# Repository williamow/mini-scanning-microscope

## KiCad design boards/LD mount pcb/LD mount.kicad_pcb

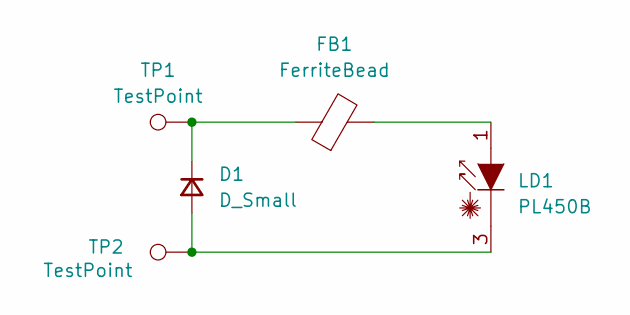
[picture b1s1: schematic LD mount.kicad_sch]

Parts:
D1: D_Small; D_SOD-123F
FB1: FerriteBead; L_0603_1608Metric_Pad1.05x0.95mm_HandSolder
LD1: PL450B; LaserDiode_TO38ICut-3
TP1, TP2: TestPoint; TestPoint_Pad_D2.0mm

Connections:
unnamed: D1.2 (A), LD1.3 (C), TP2.1
unnamed: D1.1 (K), FB1.1, TP1.1
unnamed: FB1.2, LD1.1 (A)

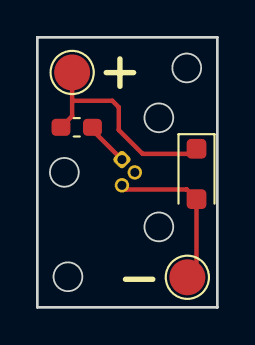
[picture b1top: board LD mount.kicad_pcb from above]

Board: 2 copper layers, 10.0 x 15.0 mm, 5 parts (1 on the bottom side), 3 nets.

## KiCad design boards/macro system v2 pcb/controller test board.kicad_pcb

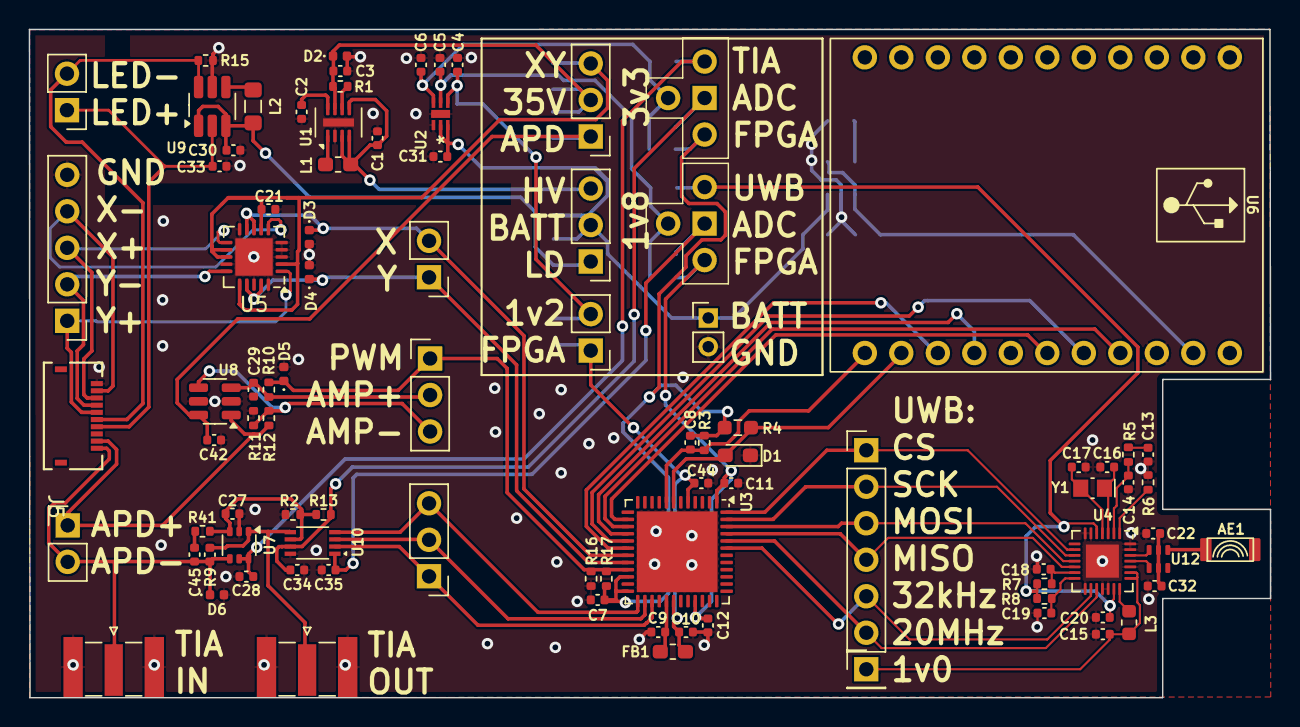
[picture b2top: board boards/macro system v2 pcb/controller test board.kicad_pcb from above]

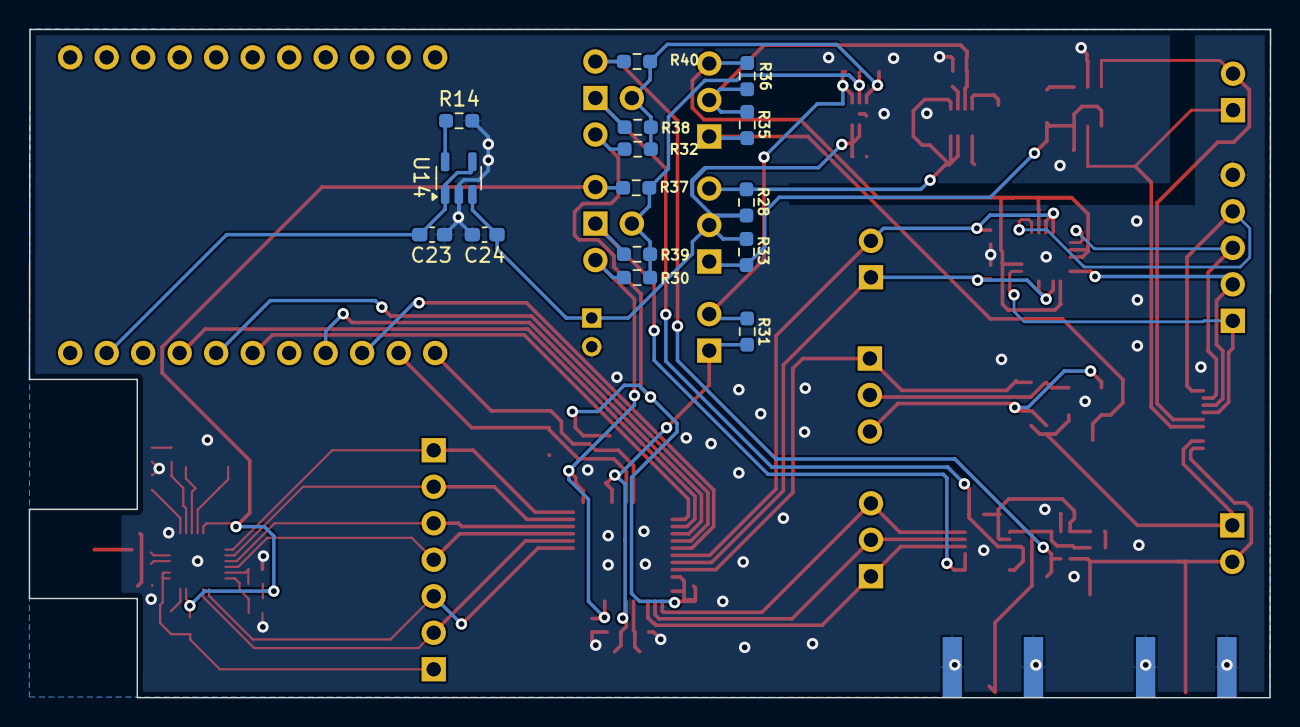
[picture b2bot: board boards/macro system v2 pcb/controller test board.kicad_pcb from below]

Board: 2 copper layers, 86.4 x 46.5 mm, 106 parts (15 on the bottom side), 69 nets.

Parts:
AE1: Antenna; antenna_footprint
C1, C3, C4, C5, C6, C15, C30, C31, C33: 1u; C_0402_1005Metric
C2: 0.22u; C_0402_1005Metric
C7, C9, C10, C11, C12, C18, C19, C20, C21, C22, C27, C28, C29, C32, C34, C35, C42, C44: 100n; C_0402_1005Metric
C8: 12p; C_0402_1005Metric
C13: 680p; C_0402_1005Metric
C14: 68p; C_0402_1005Metric
C16, C17: 3.9p; C_0402_1005Metric
C23, C24: 1u; C_0603_1608Metric_Pad1.08x0.95mm_HandSolder
C45: 50p; C_0402_1005Metric
D1: LED; LED_0603_1608Metric_Pad1.05x0.95mm_HandSolder
D2, D3, D4, D5, D6: D; D_0402_1005Metric
FB1: FerriteBead_Small; L_0603_1608Metric_Pad1.05x0.95mm_HandSolder
J1: Conn_01x02; PinHeader_1x02_P2.00mm_Vertical
J2, J6, J10, J11: Conn_01x03; PinHeader_1x03_P2.54mm_Vertical
J3, J14: Conn_Coaxial; SMA_Samtec_SMA-J-P-X-ST-EM1_EdgeMount
J4: Conn_01x06; PinHeader_1x06_P2.54mm_Vertical
J5: FH19C-10S-0.5SH10; CONN_FH19C-10S-0.5SH10_HIR
J7: Mirror drive; PinHeader_1x05_P2.54mm_Vertical
J8: mdrive; PinHeader_1x02_P2.54mm_Vertical
J9: APD_conn; PinHeader_1x02_P2.54mm_Vertical
J12: Conn_01x02; PinHeader_1x02_P2.54mm_Vertical
J15: LED conn; PinHeader_1x02_P2.54mm_Vertical
J16: Conn_01x01; PinHeader_1x01_P2.54mm_Vertical
L1: 15u; L_0603_1608Metric_Pad1.05x0.95mm_HandSolder
L2: 4.7u; L_0805_2012Metric_Pad1.05x1.20mm_HandSolder
L3: 180n; L_0603_1608Metric
R1: 5M; R_0402_1005Metric
R2, R10, R11, R13: 100k; R_0402_1005Metric
R3, R16, R17: 10k; R_0402_1005Metric
R4: 1k; R_0603_1608Metric_Pad0.98x0.95mm_HandSolder
R5: 390k; R_0402_1005Metric
R6: 2.2M; R_0402_1005Metric
R7: 380k; R_0402_1005Metric
R8: 0; R_0402_1005Metric
R9: TIA_FB; C_0402_1005Metric
R12: 1.2M; R_0402_1005Metric
R14: 10k; R_0603_1608Metric_Pad0.98x0.95mm_HandSolder
R15: 4.7; R_0402_1005Metric
R28, R30, R31, R32, R33, R35, R36, R37, R38, R39, R40: 1; R_0603_1608Metric_Pad0.98x0.95mm_HandSolder
R41: 50; R_0402_1005Metric
U1: LT3494; DFN-8-1EP_2x3mm_P0.5mm_EP0.56x2.15mm
U2: MIC5387-SG4YMT-TR; MLF-6_MT_MCH
U3: ICE40UP5K-SG48ITR; QFN-48-1EP_7x7mm_P0.5mm_EP5.6x5.6mm
U4: SR10x0; QFN-28-1EP_4x4mm_P0.4mm_EP2.3x2.3mm
U5: ADG5234_QFN; QFN-20-1EP_4x4mm_P0.5mm_EP2.6x2.6mm
U6: adafruit_FT232H
U7: OPA838SIDCKT; SOT-363_SC-70-6
U8: ADA4097; TSOT-23-6
U9: AP3036B; SOT-23-6_Handsoldering
U10: ADS7040xDCU; VSSOP-8_2.3x2mm_P0.5mm
U11, U13: Pin-T
U12: CSP_BALUN
U14: MCP73812T-420I-OT; SOT-23-5
Y1: 32.768kHz; Crystal_SMD_MicroCrystal_CM9V-T1A-2Pin_1.6x1.0mm_HandSolder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

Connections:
/1v2: C4.1, J12.2, R31.1, U2.4 (OUT3)
/1v8: C5.1, R30.1, R37.1, R39.2, U2.5 (OUT2), U13.3
/3v3: C6.1, R32.2, R38.2, R40.1, U2.6 (OUT1), U11.3
/35v: C3.1, D2.1 (K), J10.2, R1.2, R35.1, R36.1, U1.7 (VOUT)
/ADC/CS: J6.3, U3.25 (IOT_36b), U10.4 (~CS)
/ADC/SCLK: J6.1, U3.27 (IOT_38b), U10.2 (SCLK)
/ADC/SDO: J6.2, U3.26 (IOT_39a), U10.3 (SDO)
/ADC/ref: C27.1, R2.1, R13.1, R41.2, U7.3 (+), U10.6 (AINP)
/ADC/vin: J3.1 (In), R9.2, U7.1, U10.5 (AINM)
/ADG5234/INX: D3.1 (K), J8.2, U3.19 (IOB_29b), U5.8 (IN2), U5.9 (IN3)
/ADG5234/INY: D4.1 (K), J8.1, U3.20 (IOB_25b_G3), U5.17 (IN4), U5.19 (IN1)
/ADG5234/X+: J5.3, J7.3, U5.11 (D3)
/ADG5234/X-: J5.2, J7.4, U5.6 (D2)
/ADG5234/Y+: J5.5, J7.1, U5.1 (D1)
/ADG5234/Y-: J5.4, J7.2, U5.15 (D4)
/BATT: C24.1, C31.1, J1.1, J2.2, R28.1, R33.1, U2.2 (VIN), U2.3 (EN2/3), U14.3 (V_{BAT})
/HVbias/HV_bias: J5.9, J9.1, R12.2, U8.1
/HVbias/PWM_in: D5.1 (K), J11.1, R10.1, R16.1, R17.2, U3.21 (IOB_23b)
/ICE40UP5K/CLK_20.48M: J4.6, U3.44 (IOB_3b_G6), U4.17 (PLL_CLK)
/ICE40UP5K/CLK_32.768K: J4.5, U3.43 (IOT_49a), U4.16 (XTAL_CLK)
/ICE40UP5K/PROG_CDONE: D1.2 (A), R4.2, U3.7 (CDONE), U6.13 (CS4/D6)
/ICE40UP5K/PROG_CRESET: C8.2, R3.2, U3.8 (~CRESET), U6.12 (CS5/D7)
/ICE40UP5K/PROG_CS: U3.16 (IOB_35b_SPI_SS), U6.15 (CS2/D4)
/ICE40UP5K/PROG_CS2: U3.18 (IOB_31b), U6.14 (CS3/D5)
/ICE40UP5K/PROG_MISO: U3.14 (IOB_32a_SPI_SO), U6.17 (MISO/D2)
/ICE40UP5K/PROG_MOSI: U3.17 (IOB_33b_SPI_SI), U6.18 (MOSI/D1)
/ICE40UP5K/PROG_SCK: U3.15 (IOB_34a_SPI_SCK), U6.19 (SCK/D0)
/ICE40UP5K/UWB_CS: J4.1, U3.48 (IOB_4a), U4.9 (CSN)
/ICE40UP5K/UWB_MISO: J4.4, U3.45 (IOB_5b), U4.12 (MISO)
/ICE40UP5K/UWB_MOSI: J4.3, U3.46 (IOB_0a), U4.11 (MOSI)
/ICE40UP5K/UWB_SCK: J4.2, U3.47 (IOB_2a), U4.10 (SCK)
/I_35V_BATT: C1.1, J2.3, L1.1, R28.2, U1.3 (VCC), U1.4 (CTRL), U1.5 (EN)
/I_ADC_1V8: C35.1, R39.1, U10.1 (DVDD), U13.1
/I_ADC_3V3: C34.1, R13.2, R38.1, U10.7 (AVDD), U11.1
/I_FPGA_1V2: C10.1, C44.1, FB1.1, J12.1, R31.2, U3.5 (VCC), U3.30 (VCC)
/I_FPGA_1V8: C11.1, C12.1, R30.2, U3.1 (VCCIO_2), U3.33 (VCCIO_0), U13.4
/I_FPGA_3V3: C7.1, C8.1, R3.1, R4.1, R17.1, R32.1, U3.22 (SPI_VCCIO1), U3.24 (VPP_2V5), U11.4
/I_LED_BATT: C30.1, J2.1, L2.2, R33.2, U9.1 (EN), U9.3 (VIN)
/I_MIRROR_35V: C21.1, J10.3, R36.2, U5.2 (S1B), U5.7 (S2A), U5.12 (S3B), U5.13 (VDD), U5.16 (S4A)
/I_SPAD_35V: C42.1, J10.1, R35.2, U8.6 (V+)
/I_TIA_3V3: C28.1, R40.2, U7.5 (~DISABLE), U7.6 (V+), U11.2
/I_UWB_1V8: C20.1, R7.2, R8.1, R37.2, U4.5 (AVDD_3V), U4.20 (DVDD_3V), U13.2
/LED_driver/LED+: C33.1, J5.7, J15.1, U9.2 (VOUT)
/LED_driver/LED-: J5.6, J15.2, R15.2, U9.6 (FB)
/LT3494_boost/FB: R1.1, U1.6 (FB)
/SR1010_UWB/RFN: U4.25 (RFN), U12.4 (DIFFP)
/SR1010_UWB/RFP: U4.26 (RFP), U12.3 (DIFFN)
/TIA/I_APD: C45.2, D6.1 (K), J5.10, J9.2, J14.1 (In), R9.1, U7.4 (-)
GND: C1.2, C2.2, C3.2, C4.2, C5.2, C6.2, C7.2, C9.2, C10.2, C11.2, C12.2, C13.2, C14.2, C15.2, C16.2, C17.2, C18.2, C19.2, C20.2, C21.2, C22.2, C23.2, C24.2, C27.2, C28.2, C29.2, C30.2, C31.2, C32.2, C33.2, C34.2, C35.2, C42.2, C44.2, D1.1 (K), D2.2 (A), D3.2 (A), D4.2 (A), D5.2 (A), D6.2 (A), J1.2, J3.2 (Ext), J5.1, J7.5, J14.2 (Ext), R2.2, R6.1, R11.1, R14.1, R15.1, R16.2, U1.2 (GND), U1.9 (PAD), U2.1 (GND), U2.7 (PAD), U3.49 (GND), U4.6 (GND), U4.7 (SHUTDOWN), U4.15 (DVDD_NVM), U4.18 (SCAN_EN), U4.19 (DBG_EN), U4.24 (GND), U4.27 (GND), U4.28 (GND), U4.29 (PAD), U5.3 (VSS), U5.4 (GND), U5.5 (S2B), U5.10 (S3A), U5.14 (S4B), U5.18 (ENn), U5.20 (S1A), U5.21 (EP), U6.1 (GND), U6.20 (GND), U7.2 (V-), U8.2 (V-), U8.5 (~DISABLE), U9.5 (GND), U10.8 (GND), U14.2 (V_{SS})
unnamed: AE1.1 (A), U12.1 (SE(50))
unnamed: C13.1, R5.1
unnamed: C22.1, C32.1, U12.2 (GND), U12.5 (GND)
unnamed: C45.1, R41.1
unnamed: C29.1, J11.2, R10.2, U8.3 (+)
unnamed: J11.3, R11.2, R12.1, U8.4 (-)
unnamed: C15.1, J16.1, L3.1, U4.22 (DVDD_1V), U4.23 (AVDD_1V)
unnamed: C2.1, U1.8 (CAP)
unnamed: L1.2, U1.1 (SW)
unnamed: C9.1, FB1.2, U3.29 (VCCPLL)
unnamed: R6.2, U4.1 (BIAS)
unnamed: C19.1, R8.2, U4.14 (DVDD_1V8)
unnamed: C14.1, R5.2, U4.2 (PLL_TUNE)
unnamed: L3.2, U4.21 (REG_OUT)
unnamed: C18.1, R7.1, U4.13 (RSTN)
unnamed: C16.1, U4.3 (XTAL_C1), Y1.1
unnamed: C17.1, U4.4 (XTAL_C2), Y1.2
unnamed: L2.1, U9.4 (SW)
unnamed: C23.1, U6.21 (5V), U14.1 (CE), U14.4 (V_{DD})
unnamed: R14.2, U14.5 (PROG)

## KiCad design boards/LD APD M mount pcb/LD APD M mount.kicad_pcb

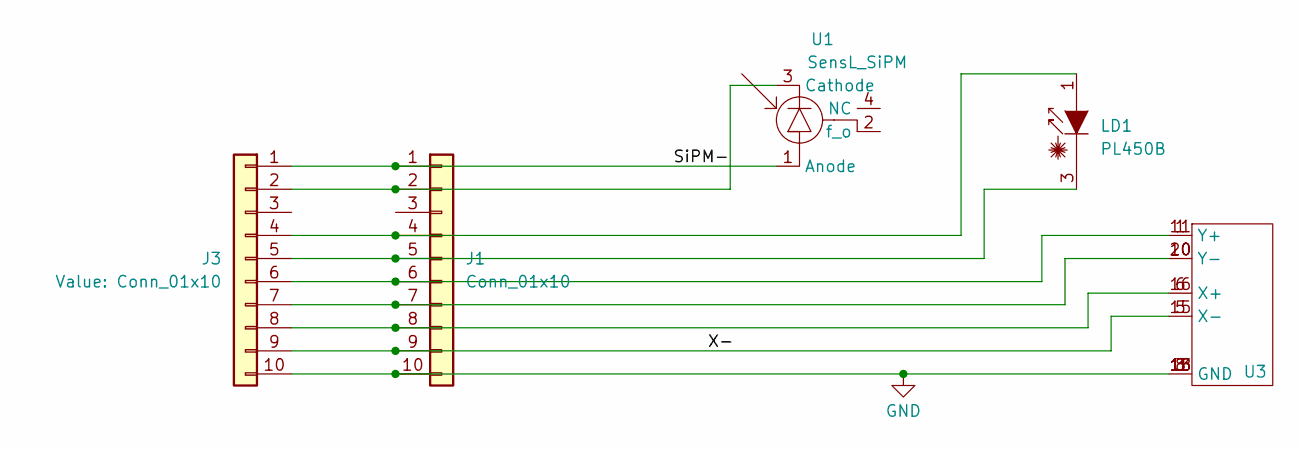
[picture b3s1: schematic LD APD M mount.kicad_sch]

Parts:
J1: Conn_01x10; PinHeader_1x10_P2.54mm_Vertical
J3: Conn_01x10; FH19C_Connector
LD1: PL450B; LaserDiode_TO38ICut-3
U1: SensL_SiPM; SensL_SiPM_6mm
U3: PLCC-20

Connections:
/SiPM-: J1.1, J3.1, U1.1 (Anode)
/X-: J1.9, J3.9, U3.5 (X-), U3.15 (X-)
GND: J1.10, J3.10, U3.3 (GND), U3.8 (GND), U3.13 (GND), U3.18 (GND)
unnamed: J1.2, J3.2, U1.3 (Cathode)
unnamed: J1.4, J3.4, LD1.1 (A)
unnamed: J1.5, J3.5, LD1.3 (C)
unnamed: J1.6, J3.6, U3.1 (Y+), U3.11 (Y+)
unnamed: J1.7, J3.7, U3.10 (Y-), U3.20 (Y-)
unnamed: J1.8, J3.8, U3.6 (X+), U3.16 (X+)

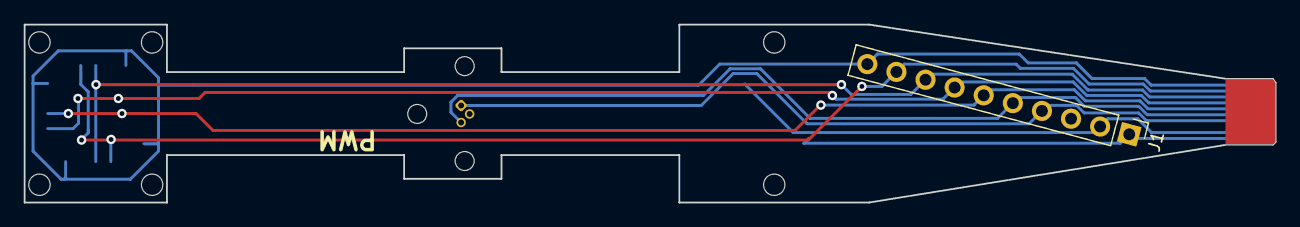
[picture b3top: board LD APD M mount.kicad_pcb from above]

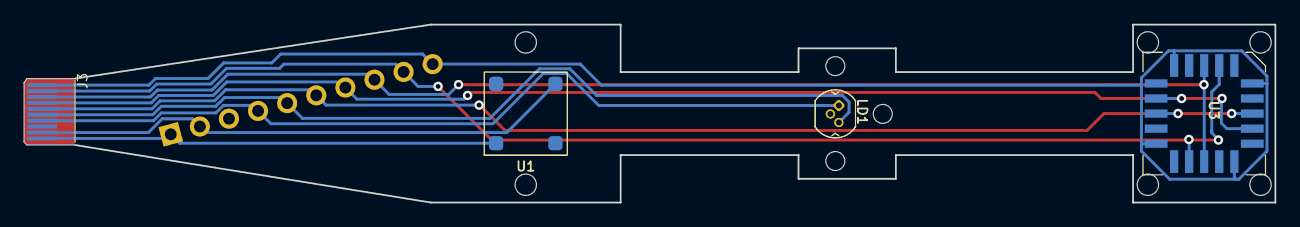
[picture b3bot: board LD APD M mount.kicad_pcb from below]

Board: 2 copper layers, 105.5 x 15.0 mm, 5 parts (4 on the bottom side), 9 nets.

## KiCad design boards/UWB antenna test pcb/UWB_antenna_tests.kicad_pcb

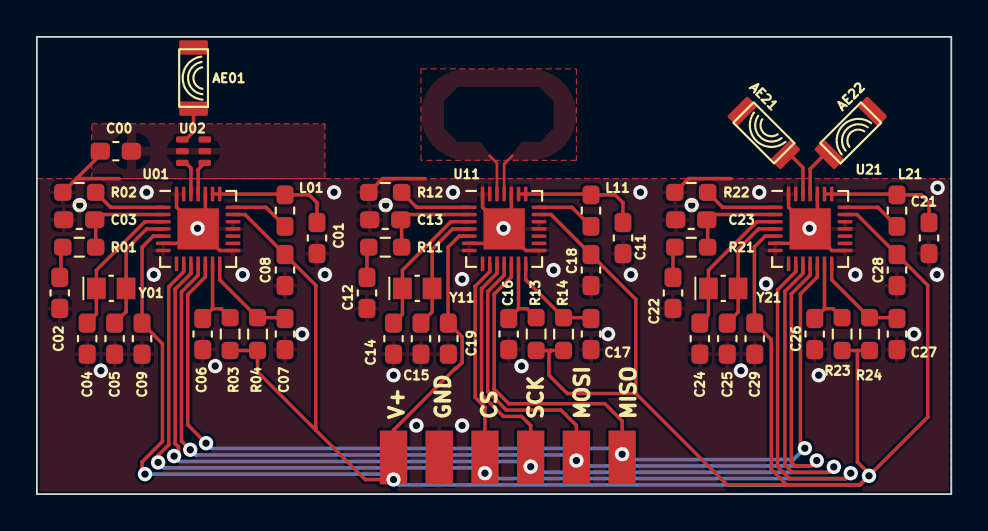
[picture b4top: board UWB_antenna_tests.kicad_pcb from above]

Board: 2 copper layers, 50.8 x 25.4 mm, 59 parts (0 on the bottom side), 40 nets.

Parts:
AE01, AE21, AE22: Antenna; antenna_footprint
C00, C06, C07, C08, C09, C16, C17, C18, C19, C26, C27, C28, C29: 100n; C_0603_1608Metric_Pad1.08x0.95mm_HandSolder
C01, C11, C21: 1u; C_0603_1608Metric_Pad1.08x0.95mm_HandSolder
C02, C12, C22: 680p; C_0603_1608Metric_Pad1.08x0.95mm_HandSolder
C03, C13, C23: 68p; C_0603_1608Metric_Pad1.08x0.95mm_HandSolder
C04, C05, C14, C15, C24, C25: 3.9p; C_0603_1608Metric_Pad1.08x0.95mm_HandSolder
J1, J2, J3, J4, J5, J6: Conn_01x01; modular_pinhead_SMD
L01, L11, L21: 180n; L_0603_1608Metric_Pad1.05x0.95mm_HandSolder
R01, R11, R21: 390k; R_0603_1608Metric_Pad0.98x0.95mm_HandSolder
R02, R12, R22: 2.2M; R_0603_1608Metric_Pad0.98x0.95mm_HandSolder
R03, R13, R23: 380k; R_0603_1608Metric_Pad0.98x0.95mm_HandSolder
R04, R14, R24: 0; R_0603_1608Metric_Pad0.98x0.95mm_HandSolder
U01, U11, U21: SR10x0; QFN-28-1EP_4x4mm_P0.4mm_EP2.3x2.3mm
U02: CSP_BALUN
Y01, Y11, Y21: 32.768kHz; Crystal_SMD_MicroCrystal_CM9V-T1A-2Pin_1.6x1.0mm_HandSolder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

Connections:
/UWB radio cap coupled1/1v8: C08.1, C09.1, C18.1, C19.1, C28.1, C29.1, J1.1, R03.2, R04.1, R13.2, R14.1, R23.2, R24.1, U01.5 (AVDD_3V), U01.20 (DVDD_3V), U11.5 (AVDD_3V), U11.20 (DVDD_3V), U21.5 (AVDD_3V), U21.20 (DVDD_3V)
/UWB radio cap coupled1/CS: J6.1, U01.9 (CSN), U11.9 (CSN), U21.9 (CSN)
/UWB radio cap coupled1/MISO: J5.1, U01.12 (MISO), U11.12 (MISO), U21.12 (MISO)
/UWB radio cap coupled1/MOSI: J3.1, U01.11 (MOSI), U11.11 (MOSI), U21.11 (MOSI)
/UWB radio cap coupled1/RFN: U01.25 (RFN), U02.4 (DIFFP)
/UWB radio cap coupled1/RFP: U01.26 (RFP), U02.3 (DIFFN)
/UWB radio cap coupled1/SCK: J4.1, U01.10 (SCK), U11.10 (SCK), U21.10 (SCK)
/UWB radio cap coupled2/RFN: U11.25 (RFN), U11.26 (RFP)
/UWB radio cap coupled3/RFN: AE22.1 (A), U21.25 (RFN)
/UWB radio cap coupled3/RFP: AE21.1 (A), U21.26 (RFP)
GND: C00.2, C01.2, C02.2, C03.2, C04.2, C05.2, C06.2, C07.2, C08.2, C09.2, C11.2, C12.2, C13.2, C14.2, C15.2, C16.2, C17.2, C18.2, C19.2, C21.2, C22.2, C23.2, C24.2, C25.2, C26.2, C27.2, C28.2, C29.2, J2.1, R02.1, R12.1, R22.1, U01.6 (GND), U01.7 (SHUTDOWN), U01.15 (DVDD_NVM), U01.18 (SCAN_EN), U01.19 (DBG_EN), U01.24 (GND), U01.27 (GND), U01.28 (GND), U01.29 (PAD), U11.6 (GND), U11.7 (SHUTDOWN), U11.15 (DVDD_NVM), U11.18 (SCAN_EN), U11.19 (DBG_EN), U11.24 (GND), U11.27 (GND), U11.28 (GND), U11.29 (PAD), U21.6 (GND), U21.7 (SHUTDOWN), U21.15 (DVDD_NVM), U21.18 (SCAN_EN), U21.19 (DBG_EN), U21.24 (GND), U21.27 (GND), U21.28 (GND), U21.29 (PAD)
unnamed: AE01.1 (A), U02.1 (SE(50))
unnamed: C00.1, U02.2 (GND), U02.5 (GND)
unnamed: C01.1, L01.1, U01.22 (DVDD_1V), U01.23 (AVDD_1V)
unnamed: C02.1, R01.1
unnamed: C03.1, R01.2, U01.2 (PLL_TUNE)
unnamed: C04.1, U01.3 (XTAL_C1), Y01.1
unnamed: C05.1, U01.4 (XTAL_C2), Y01.2
unnamed: C06.1, R03.1, U01.13 (RSTN)
unnamed: C07.1, R04.2, U01.14 (DVDD_1V8)
unnamed: C11.1, L11.1, U11.22 (DVDD_1V), U11.23 (AVDD_1V)
unnamed: C12.1, R11.1
unnamed: C13.1, R11.2, U11.2 (PLL_TUNE)
unnamed: C14.1, U11.3 (XTAL_C1), Y11.1
unnamed: C15.1, U11.4 (XTAL_C2), Y11.2
unnamed: C16.1, R13.1, U11.13 (RSTN)
unnamed: C17.1, R14.2, U11.14 (DVDD_1V8)
unnamed: C21.1, L21.1, U21.22 (DVDD_1V), U21.23 (AVDD_1V)
unnamed: C22.1, R21.1
unnamed: C23.1, R21.2, U21.2 (PLL_TUNE)
unnamed: C24.1, U21.3 (XTAL_C1), Y21.1
unnamed: C25.1, U21.4 (XTAL_C2), Y21.2
unnamed: C26.1, R23.1, U21.13 (RSTN)
unnamed: C27.1, R24.2, U21.14 (DVDD_1V8)
unnamed: L01.2, U01.21 (REG_OUT)
unnamed: L11.2, U11.21 (REG_OUT)
unnamed: L21.2, U21.21 (REG_OUT)
unnamed: R02.2, U01.1 (BIAS)
unnamed: R12.2, U11.1 (BIAS)
unnamed: R22.2, U21.1 (BIAS)

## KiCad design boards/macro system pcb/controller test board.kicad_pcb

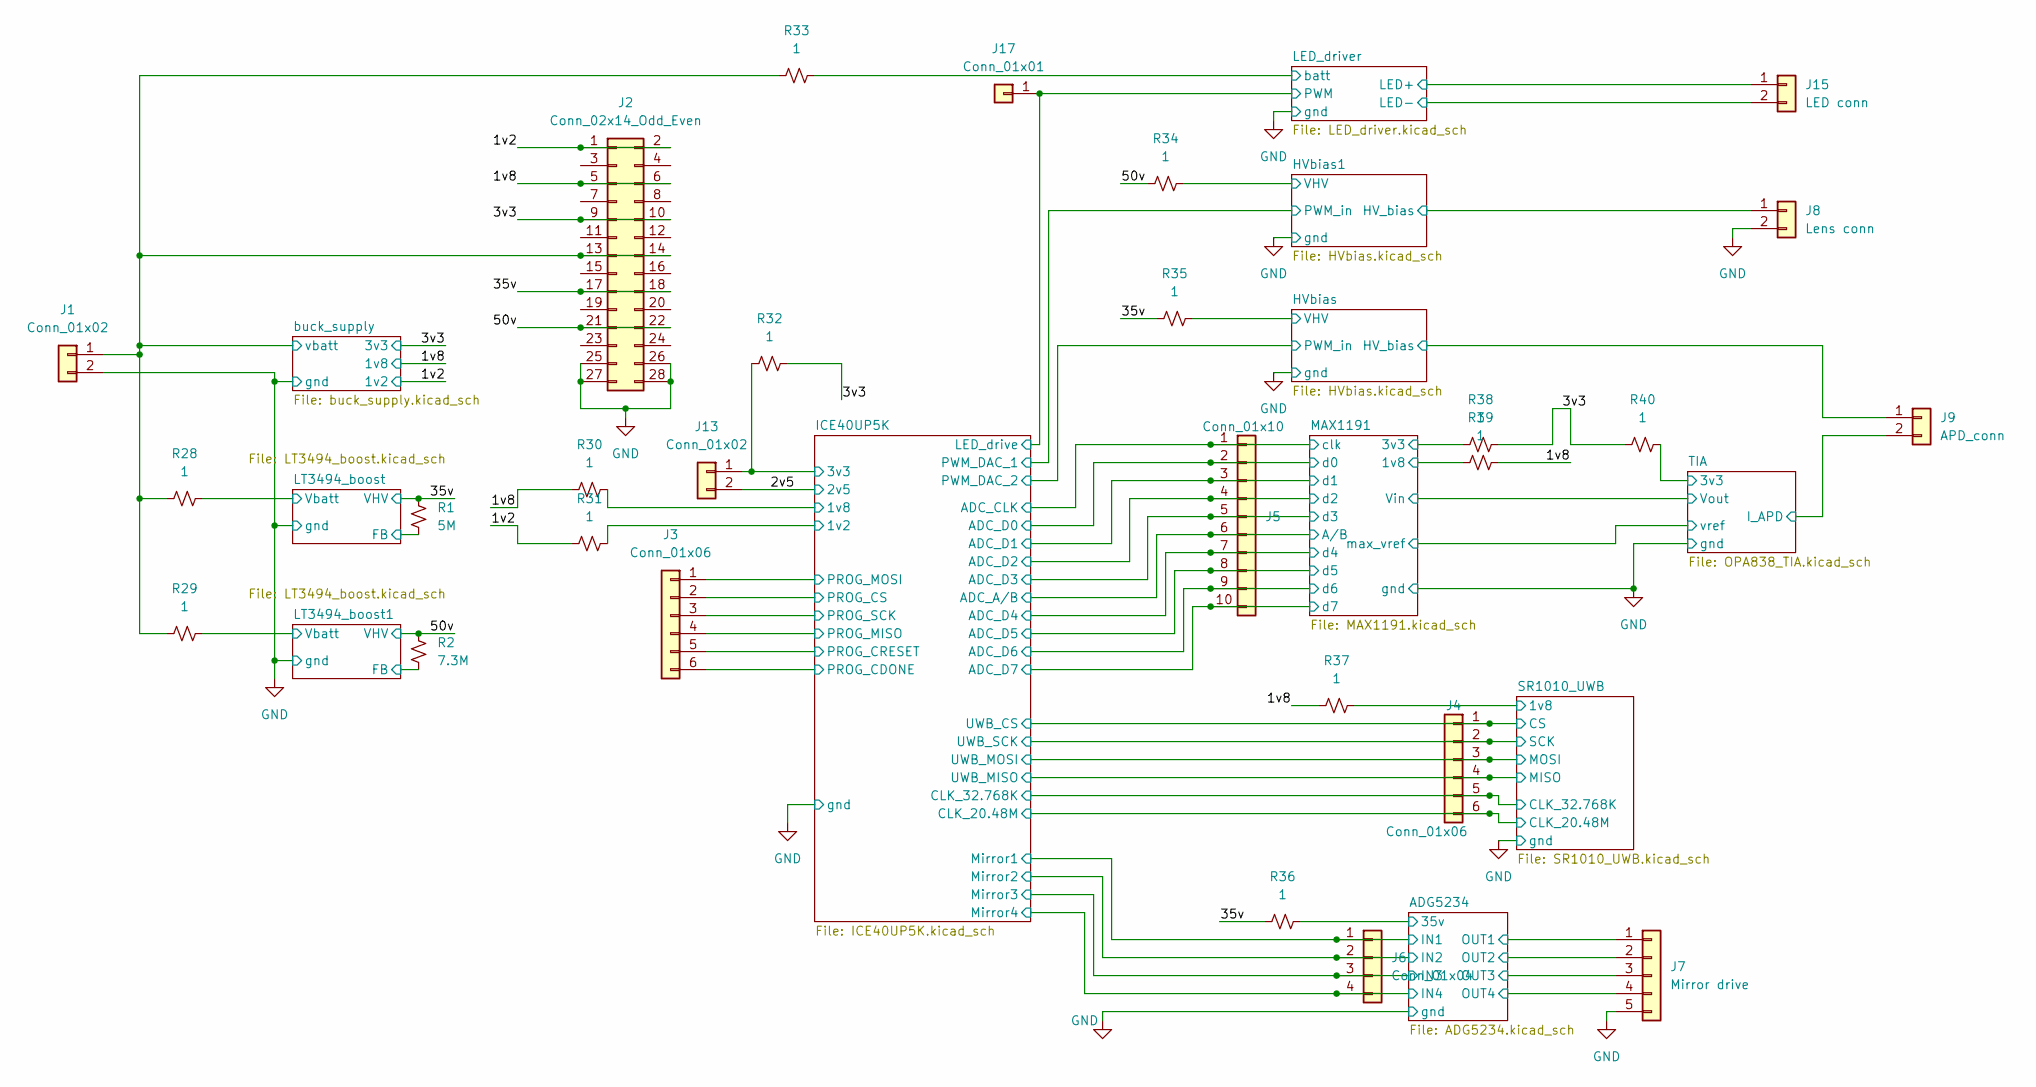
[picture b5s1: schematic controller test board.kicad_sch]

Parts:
J1, J13: Conn_01x02; PinHeader_1x02_P2.54mm_Vertical
J2: Conn_02x14_Odd_Even; PinHeader_2x14_P2.54mm_Vertical
J3, J4: Conn_01x06; PinHeader_1x06_P2.54mm_Vertical
J5: Conn_01x10; PinHeader_1x10_P2.54mm_Vertical
J6: Conn_01x04; PinHeader_1x04_P2.54mm_Vertical
J7: Mirror drive; PinHeader_1x05_P2.54mm_Vertical
J8: Lens conn; PinHeader_1x02_P2.54mm_Vertical
J9: APD_conn; PinHeader_1x02_P2.54mm_Vertical
J15: LED conn; PinHeader_1x02_P2.54mm_Vertical
J17: Conn_01x01; PinHeader_1x01_P2.54mm_Vertical
R1: 5M; R_0603_1608Metric_Pad0.98x0.95mm_HandSolder
R2: 7.3M; R_0603_1608Metric_Pad0.98x0.95mm_HandSolder
R28, R29, R30, R31, R32, R33, R34, R35, R36, R37, R38, R39, R40: 1; R_0603_1608Metric_Pad0.98x0.95mm_HandSolder

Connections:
/1v2: J2.1, J2.2, R31.1; also elsewhere on the board
/1v8: J2.5, J2.6, R30.1, R37.1, R39.2; also elsewhere on the board
/2v5: J13.2; also elsewhere on the board
/3v3: J2.9, J2.10, R32.2, R38.2, R40.1; also elsewhere on the board
/35v: J2.17, J2.18, R1.2, R35.1, R36.1; also elsewhere on the board
/50v: J2.21, J2.22, R2.2, R34.1; also elsewhere on the board
/ADG5234/35v: R36.2; also elsewhere on the board
/ADG5234/IN1: J6.1; also elsewhere on the board
/ADG5234/IN2: J6.2; also elsewhere on the board
/ADG5234/IN3: J6.3; also elsewhere on the board
/ADG5234/IN4: J6.4; also elsewhere on the board
/ADG5234/OUT1: J7.1; also elsewhere on the board
/ADG5234/OUT2: J7.2; also elsewhere on the board
/ADG5234/OUT3: J7.3; also elsewhere on the board
/ADG5234/OUT4: J7.4; also elsewhere on the board
/HVbias1/HV_bias: J8.1; also elsewhere on the board
/HVbias1/VHV: R34.2; also elsewhere on the board
/HVbias/HV_bias: J9.1; also elsewhere on the board
/HVbias/VHV: R35.2; also elsewhere on the board
/ICE40UP5K/1v2: R31.2; also elsewhere on the board
/ICE40UP5K/1v8: R30.2; also elsewhere on the board
/ICE40UP5K/3v3: J13.1, R32.1; also elsewhere on the board
/ICE40UP5K/ADC_A/B: J5.6; also elsewhere on the board
/ICE40UP5K/ADC_CLK: J5.1; also elsewhere on the board
/ICE40UP5K/ADC_D0: J5.2; also elsewhere on the board
/ICE40UP5K/ADC_D1: J5.3; also elsewhere on the board
/ICE40UP5K/ADC_D2: J5.4; also elsewhere on the board
/ICE40UP5K/ADC_D3: J5.5; also elsewhere on the board
/ICE40UP5K/ADC_D4: J5.7; also elsewhere on the board
/ICE40UP5K/ADC_D5: J5.8; also elsewhere on the board
/ICE40UP5K/ADC_D6: J5.9; also elsewhere on the board
/ICE40UP5K/ADC_D7: J5.10; also elsewhere on the board
/ICE40UP5K/CLK_20.48M: J4.6; also elsewhere on the board
/ICE40UP5K/CLK_32.768K: J4.5; also elsewhere on the board
/ICE40UP5K/LED_drive: J17.1; also elsewhere on the board
/ICE40UP5K/PROG_CDONE: J3.6; also elsewhere on the board
/ICE40UP5K/PROG_CRESET: J3.5; also elsewhere on the board
/ICE40UP5K/PROG_CS: J3.2; also elsewhere on the board
/ICE40UP5K/PROG_MISO: J3.4; also elsewhere on the board
/ICE40UP5K/PROG_MOSI: J3.1; also elsewhere on the board
/ICE40UP5K/PROG_SCK: J3.3; also elsewhere on the board
/ICE40UP5K/UWB_CS: J4.1; also elsewhere on the board
/ICE40UP5K/UWB_MISO: J4.4; also elsewhere on the board
/ICE40UP5K/UWB_MOSI: J4.3; also elsewhere on the board
/ICE40UP5K/UWB_SCK: J4.2; also elsewhere on the board
/LED_driver/LED+: J15.1; also elsewhere on the board
/LED_driver/LED-: J15.2; also elsewhere on the board
/LED_driver/batt: R33.2; also elsewhere on the board
/LT3494_boost1/FB: R2.1; also elsewhere on the board
/LT3494_boost1/Vbatt: R29.2; also elsewhere on the board
/LT3494_boost/FB: R1.1; also elsewhere on the board
/LT3494_boost/Vbatt: R28.2; also elsewhere on the board
/MAX1191/1v8: R39.1; also elsewhere on the board
/MAX1191/3v3: R38.1; also elsewhere on the board
/SR1010_UWB/1v8: R37.2; also elsewhere on the board
/TIA/3v3: R40.2; also elsewhere on the board
/TIA/I_APD: J9.2; also elsewhere on the board
/buck_supply/vbatt: J1.1, J2.13, J2.14, R28.1, R29.1, R33.1; also elsewhere on the board
GND: J1.2, J2.25, J2.26, J2.27, J2.28, J7.5, J8.2; also elsewhere on the board

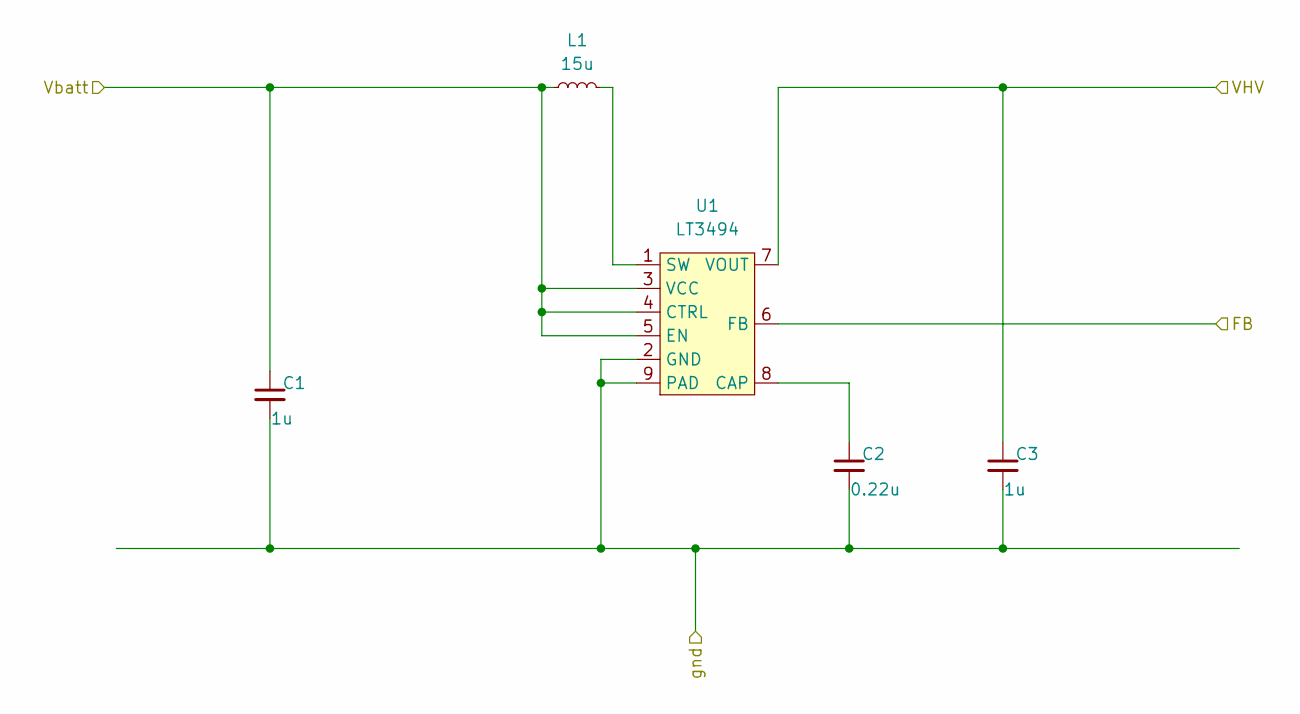
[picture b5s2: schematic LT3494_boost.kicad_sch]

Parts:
C1, C3: 1u; C_0603_1608Metric_Pad1.08x0.95mm_HandSolder
C2: 0.22u; C_0603_1608Metric_Pad1.08x0.95mm_HandSolder
L1: 15u; L_0603_1608Metric_Pad1.05x0.95mm_HandSolder
U1: LT3494; DFN-8-1EP_2x3mm_P0.5mm_EP0.56x2.15mm

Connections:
/35v: C3.1, U1.7 (VOUT); also elsewhere on the board
/LT3494_boost/FB: U1.6 (FB); also elsewhere on the board
/LT3494_boost/Vbatt: C1.1, L1.1, U1.3 (VCC), U1.4 (CTRL), U1.5 (EN); also elsewhere on the board
GND: C1.2, C2.2, C3.2, U1.2 (GND), U1.9 (PAD); also elsewhere on the board
unnamed: C2.1, U1.8 (CAP)
unnamed: L1.2, U1.1 (SW)

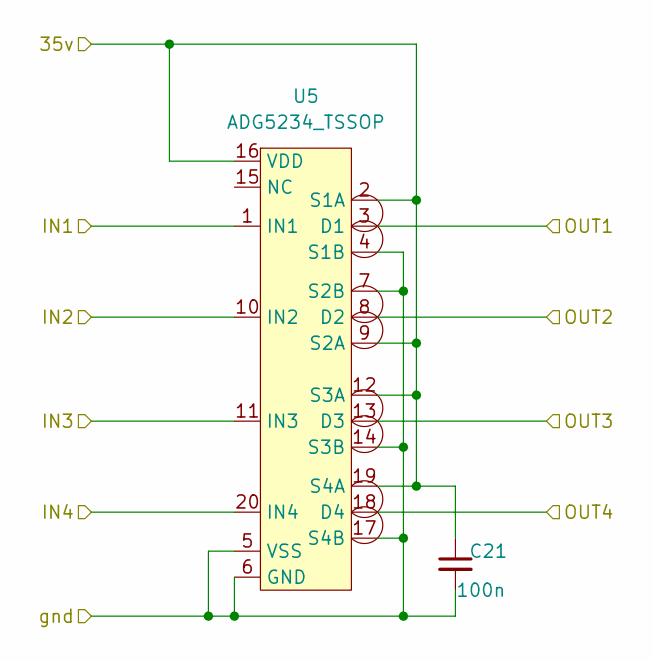
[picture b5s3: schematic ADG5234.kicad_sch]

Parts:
C21: 100n; C_0603_1608Metric_Pad1.08x0.95mm_HandSolder
U5: ADG5234_TSSOP; TSSOP-20_4.4x6.5mm_P0.65mm

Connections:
/ADG5234/35v: C21.1, U5.2 (S1A), U5.9 (S2A), U5.12 (S3A), U5.16 (VDD), U5.19 (S4A); also elsewhere on the board
/ADG5234/IN1: U5.1 (IN1); also elsewhere on the board
/ADG5234/IN2: U5.10 (IN2); also elsewhere on the board
/ADG5234/IN3: U5.11 (IN3); also elsewhere on the board
/ADG5234/IN4: U5.20 (IN4); also elsewhere on the board
/ADG5234/OUT1: U5.3 (D1); also elsewhere on the board
/ADG5234/OUT2: U5.8 (D2); also elsewhere on the board
/ADG5234/OUT3: U5.13 (D3); also elsewhere on the board
/ADG5234/OUT4: U5.18 (D4); also elsewhere on the board
GND: C21.2, U5.4 (S1B), U5.5 (VSS), U5.6 (GND), U5.7 (S2B), U5.14 (S3B), U5.17 (S4B); also elsewhere on the board

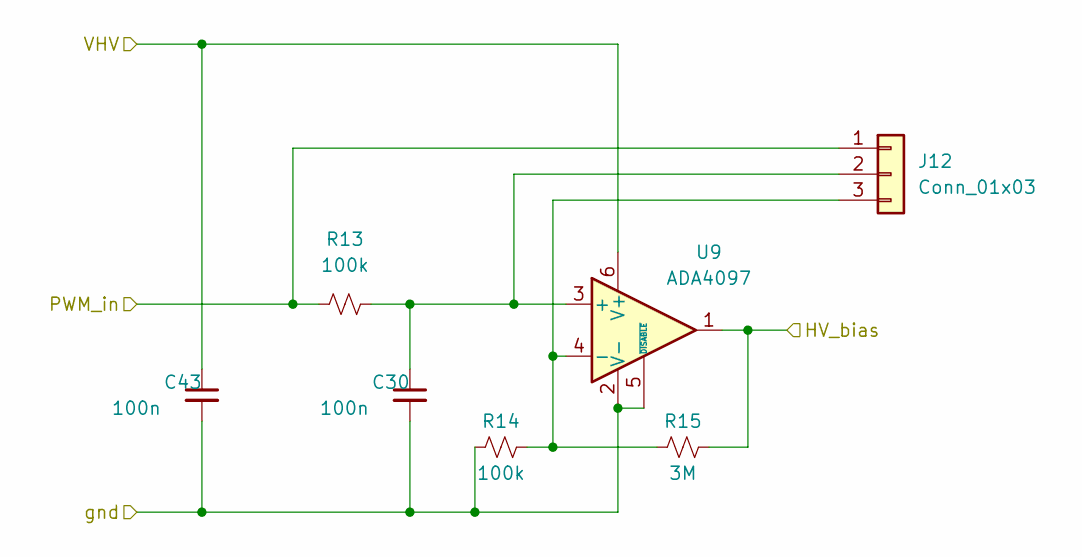
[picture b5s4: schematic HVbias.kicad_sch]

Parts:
C30, C43: 100n; C_0603_1608Metric_Pad1.08x0.95mm_HandSolder
J12: Conn_01x03; PinHeader_1x03_P2.54mm_Vertical
R13, R14: 100k; R_0603_1608Metric_Pad0.98x0.95mm_HandSolder
R15: 3M; R_0603_1608Metric_Pad0.98x0.95mm_HandSolder
U9: ADA4097; TSOT-23-6_HandSoldering

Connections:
/HVbias1/HV_bias: R15.2, U9.1; also elsewhere on the board
/HVbias1/PWM_in: J12.1, R13.1; also elsewhere on the board
/HVbias1/VHV: C43.1, U9.6 (V+); also elsewhere on the board
GND: C30.2, C43.2, R14.1, U9.2 (V-), U9.5 (~DISABLE); also elsewhere on the board
unnamed: C30.1, J12.2, R13.2, U9.3 (+)
unnamed: J12.3, R14.2, R15.1, U9.4 (-)

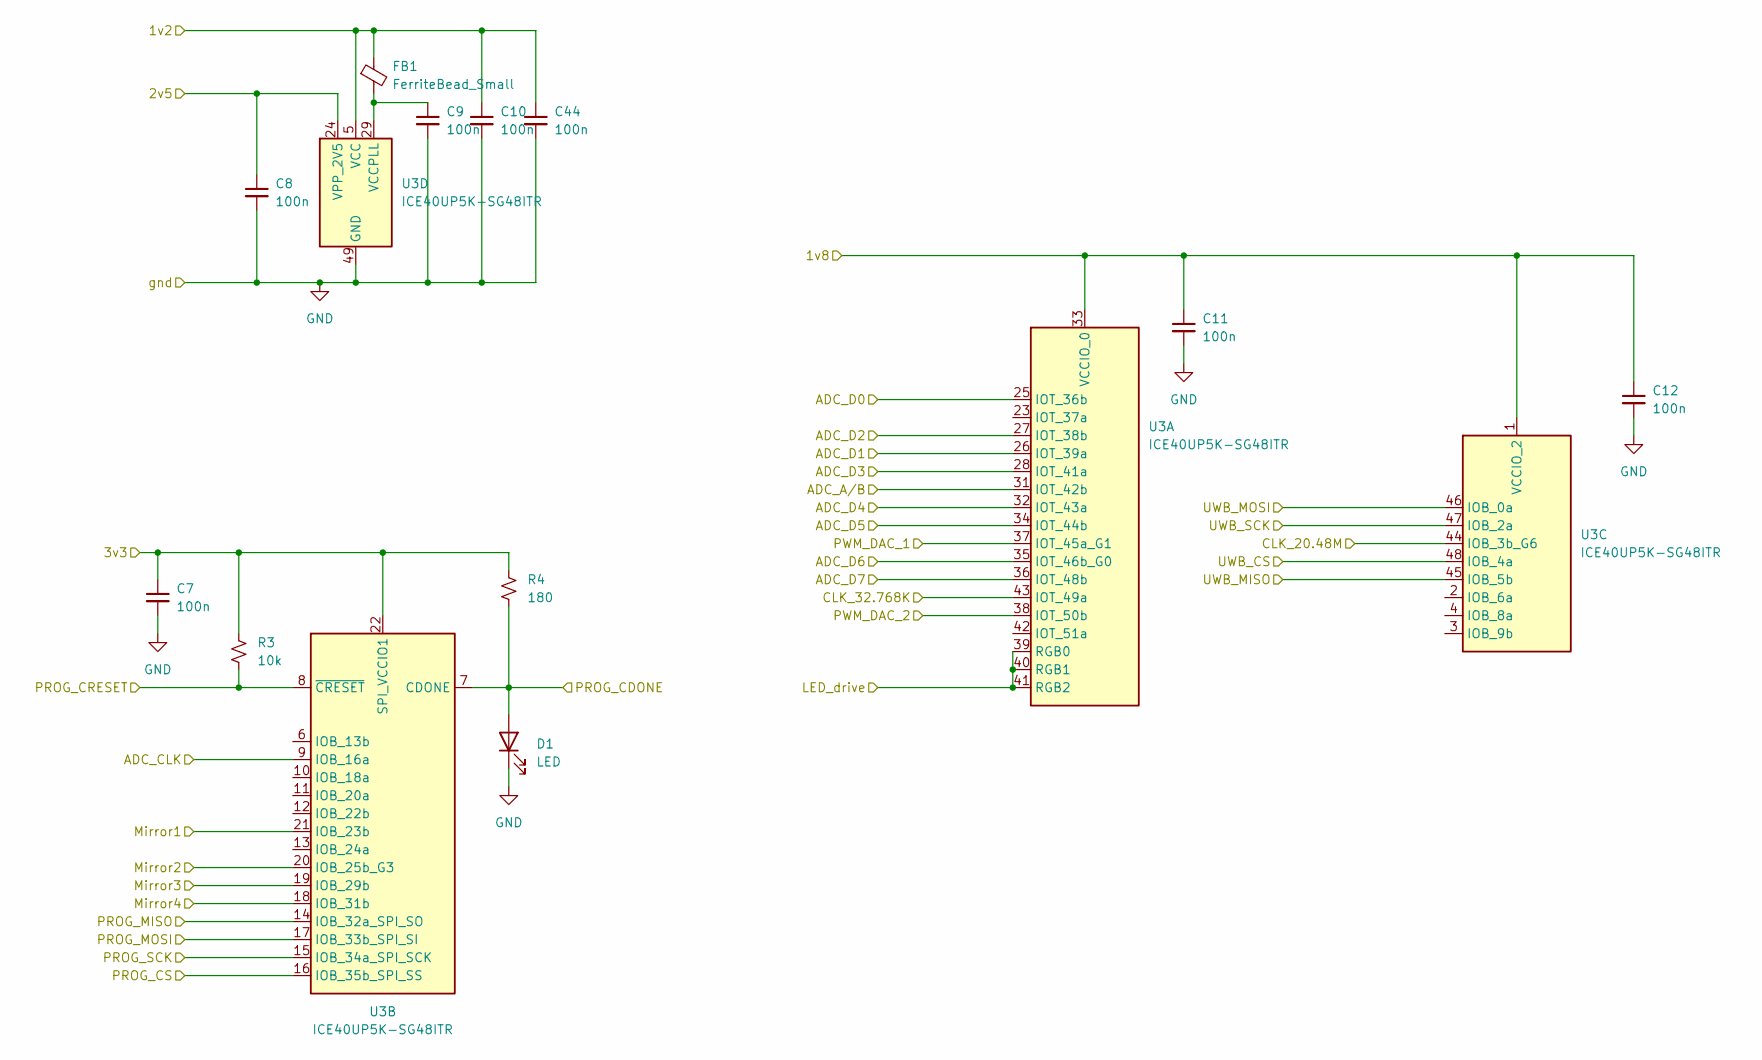
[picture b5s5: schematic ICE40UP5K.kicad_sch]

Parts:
C7, C8, C9, C10, C11, C12, C44: 100n; C_0603_1608Metric_Pad1.08x0.95mm_HandSolder
D1: LED; LED_0603_1608Metric_Pad1.05x0.95mm_HandSolder
FB1: FerriteBead_Small; L_0603_1608Metric_Pad1.05x0.95mm_HandSolder
R3: 10k; R_0603_1608Metric_Pad0.98x0.95mm_HandSolder
R4: 180; R_0603_1608Metric_Pad0.98x0.95mm_HandSolder
U3: ICE40UP5K-SG48ITR; QFN-48-1EP_7x7mm_P0.5mm_EP5.6x5.6mm

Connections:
/2v5: C8.1, U3.24 (VPP_2V5); also elsewhere on the board
/ADG5234/IN1: U3.21 (IOB_23b); also elsewhere on the board
/ADG5234/IN2: U3.20 (IOB_25b_G3); also elsewhere on the board
/ADG5234/IN3: U3.19 (IOB_29b); also elsewhere on the board
/ADG5234/IN4: U3.18 (IOB_31b); also elsewhere on the board
/HVbias1/PWM_in: U3.37 (IOT_45a_G1); also elsewhere on the board
/HVbias/PWM_in: U3.38 (IOT_50b); also elsewhere on the board
/ICE40UP5K/1v2: C10.1, C44.1, FB1.1, U3.5 (VCC), U3.30 (VCC); also elsewhere on the board
/ICE40UP5K/1v8: C11.1, C12.1, U3.1 (VCCIO_2), U3.33 (VCCIO_0); also elsewhere on the board
/ICE40UP5K/3v3: C7.1, R3.1, R4.1, U3.22 (SPI_VCCIO1); also elsewhere on the board
/ICE40UP5K/ADC_A/B: U3.31 (IOT_42b); also elsewhere on the board
/ICE40UP5K/ADC_CLK: U3.9 (IOB_16a); also elsewhere on the board
/ICE40UP5K/ADC_D0: U3.25 (IOT_36b); also elsewhere on the board
/ICE40UP5K/ADC_D1: U3.26 (IOT_39a); also elsewhere on the board
/ICE40UP5K/ADC_D2: U3.27 (IOT_38b); also elsewhere on the board
/ICE40UP5K/ADC_D3: U3.28 (IOT_41a); also elsewhere on the board
/ICE40UP5K/ADC_D4: U3.32 (IOT_43a); also elsewhere on the board
/ICE40UP5K/ADC_D5: U3.34 (IOT_44b); also elsewhere on the board
/ICE40UP5K/ADC_D6: U3.35 (IOT_46b_G0); also elsewhere on the board
/ICE40UP5K/ADC_D7: U3.36 (IOT_48b); also elsewhere on the board
/ICE40UP5K/CLK_20.48M: U3.44 (IOB_3b_G6); also elsewhere on the board
/ICE40UP5K/CLK_32.768K: U3.43 (IOT_49a); also elsewhere on the board
/ICE40UP5K/LED_drive: U3.39 (RGB0), U3.40 (RGB1), U3.41 (RGB2); also elsewhere on the board
/ICE40UP5K/PROG_CDONE: D1.2 (A), R4.2, U3.7 (CDONE); also elsewhere on the board
/ICE40UP5K/PROG_CRESET: R3.2, U3.8 (~CRESET); also elsewhere on the board
/ICE40UP5K/PROG_CS: U3.16 (IOB_35b_SPI_SS); also elsewhere on the board
/ICE40UP5K/PROG_MISO: U3.14 (IOB_32a_SPI_SO); also elsewhere on the board
/ICE40UP5K/PROG_MOSI: U3.17 (IOB_33b_SPI_SI); also elsewhere on the board
/ICE40UP5K/PROG_SCK: U3.15 (IOB_34a_SPI_SCK); also elsewhere on the board
/ICE40UP5K/UWB_CS: U3.48 (IOB_4a); also elsewhere on the board
/ICE40UP5K/UWB_MISO: U3.45 (IOB_5b); also elsewhere on the board
/ICE40UP5K/UWB_MOSI: U3.46 (IOB_0a); also elsewhere on the board
/ICE40UP5K/UWB_SCK: U3.47 (IOB_2a); also elsewhere on the board
GND: C7.2, C8.2, C9.2, C10.2, C11.2, C12.2, C44.2, D1.1 (K), U3.49 (GND); also elsewhere on the board
unnamed: C9.1, FB1.2, U3.29 (VCCPLL)
